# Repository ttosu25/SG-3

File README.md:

# Overview

Strain gauges produce very small differential voltage signals that encode information about mechanical strain. Precise and accurate measurement requires careful analogue signal conditioning before digitisation, followed by digital signal processing to extract the desired measurement. This project explores the design of a complete measurement device, from sensor excitation and analogue front-end conditioning through to digital acquisition, processing, and display output.

# System Block Diagram

# Key Design Features

## AC Current Excitation

Current-driven AC excitation: Current excitation improves the linearity between applied strain and differential bridge output. Using AC rather than DC excitation reduces measurement offset and drift, mitigates low frequency (1/f) noise, and suppresses parasitic thermoelectric effects.
  
## Bessel Filtering
The Bessel response was selected for its absence of overshoot and steeper amplitude roll-off compared with the Butterworth response. The filter also exhibits minimal passband variation and a simulated settling time of 7 ms, which is significantly shorter than the latency introduced by the sigma-delta ADC's digital filtering.

## Oversampled Sigma Delta ADC
Sigma-Delta converters contain integrated features such as digital filters that minimise the effect of extrinsic and intrinsic noise sources such as alias signal noise, 50/60hz power noise, RF noise pick up and clock jitter. The Oversampling nature of Sigma-Delta converts also distributes noise over a wider range of frequencies which reduces the effect of quantisation noise.

# Schematic

# PCB Layout and Tracing

# 3D model view

# Repository Structure

hardware/ — Contains the schematics, PCB layout files, Gerber files, MCU pin assignment, and hardware revisions.

tr/ — Contains technical research and supporting analysis, including datasheets, application notes, initial problem-space exploration, and SPICE simulations with FFT analysis.

docs/ — Contains the project specification, design documentation, and system diagrams.

firmware/ — Contains the programs running on the MCU for the embedded application.

Logbook entries not available.

# Status
Prototyping Stage, PCB fabricated.

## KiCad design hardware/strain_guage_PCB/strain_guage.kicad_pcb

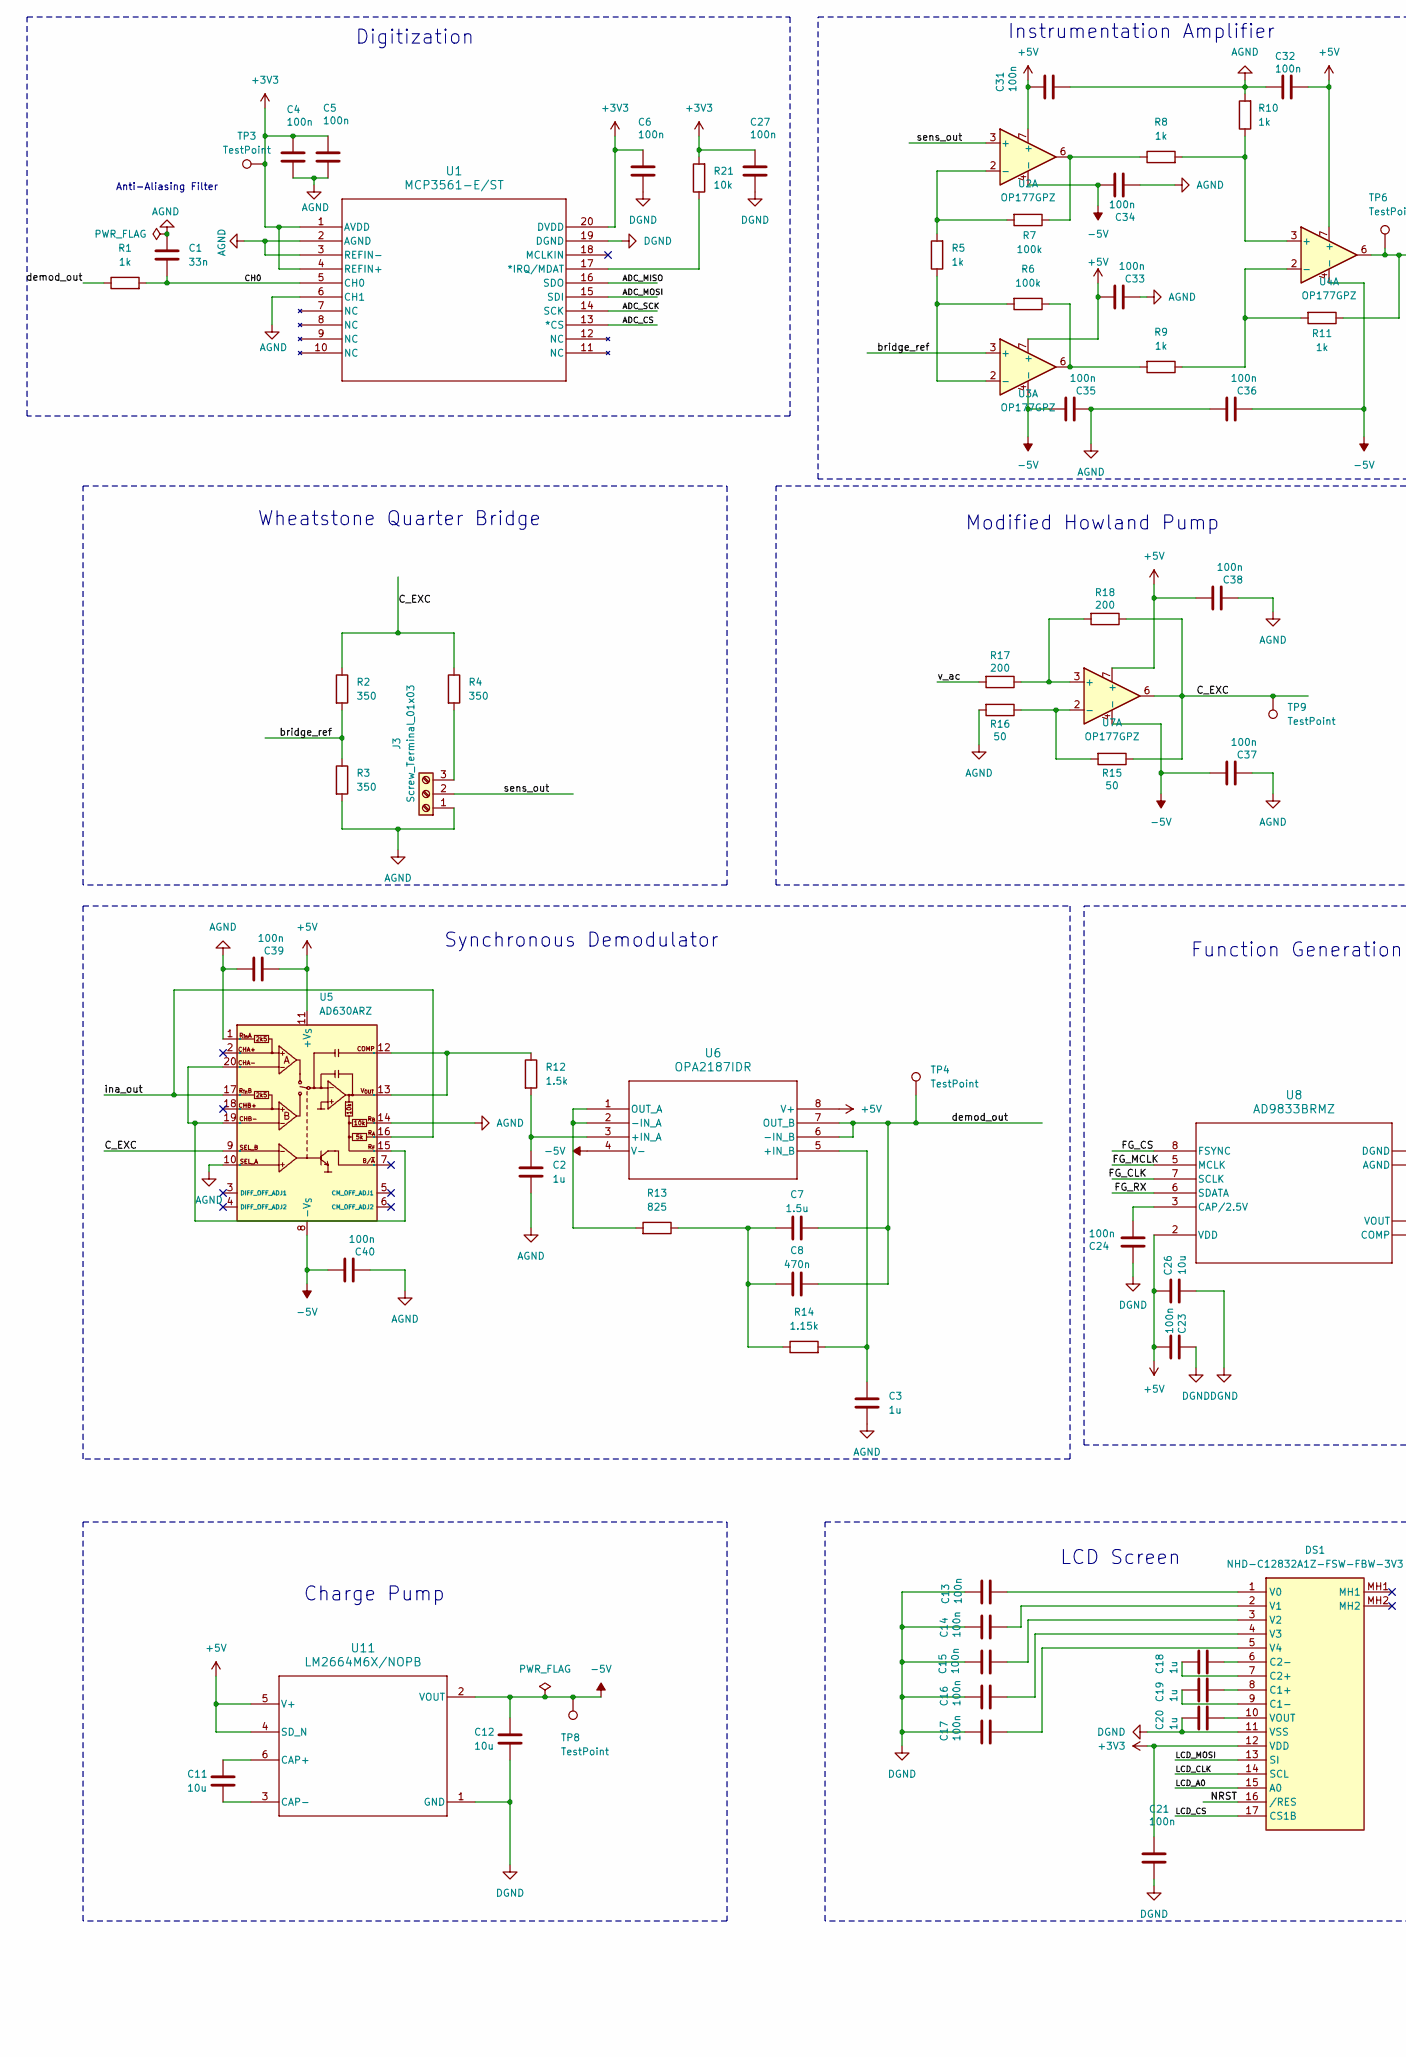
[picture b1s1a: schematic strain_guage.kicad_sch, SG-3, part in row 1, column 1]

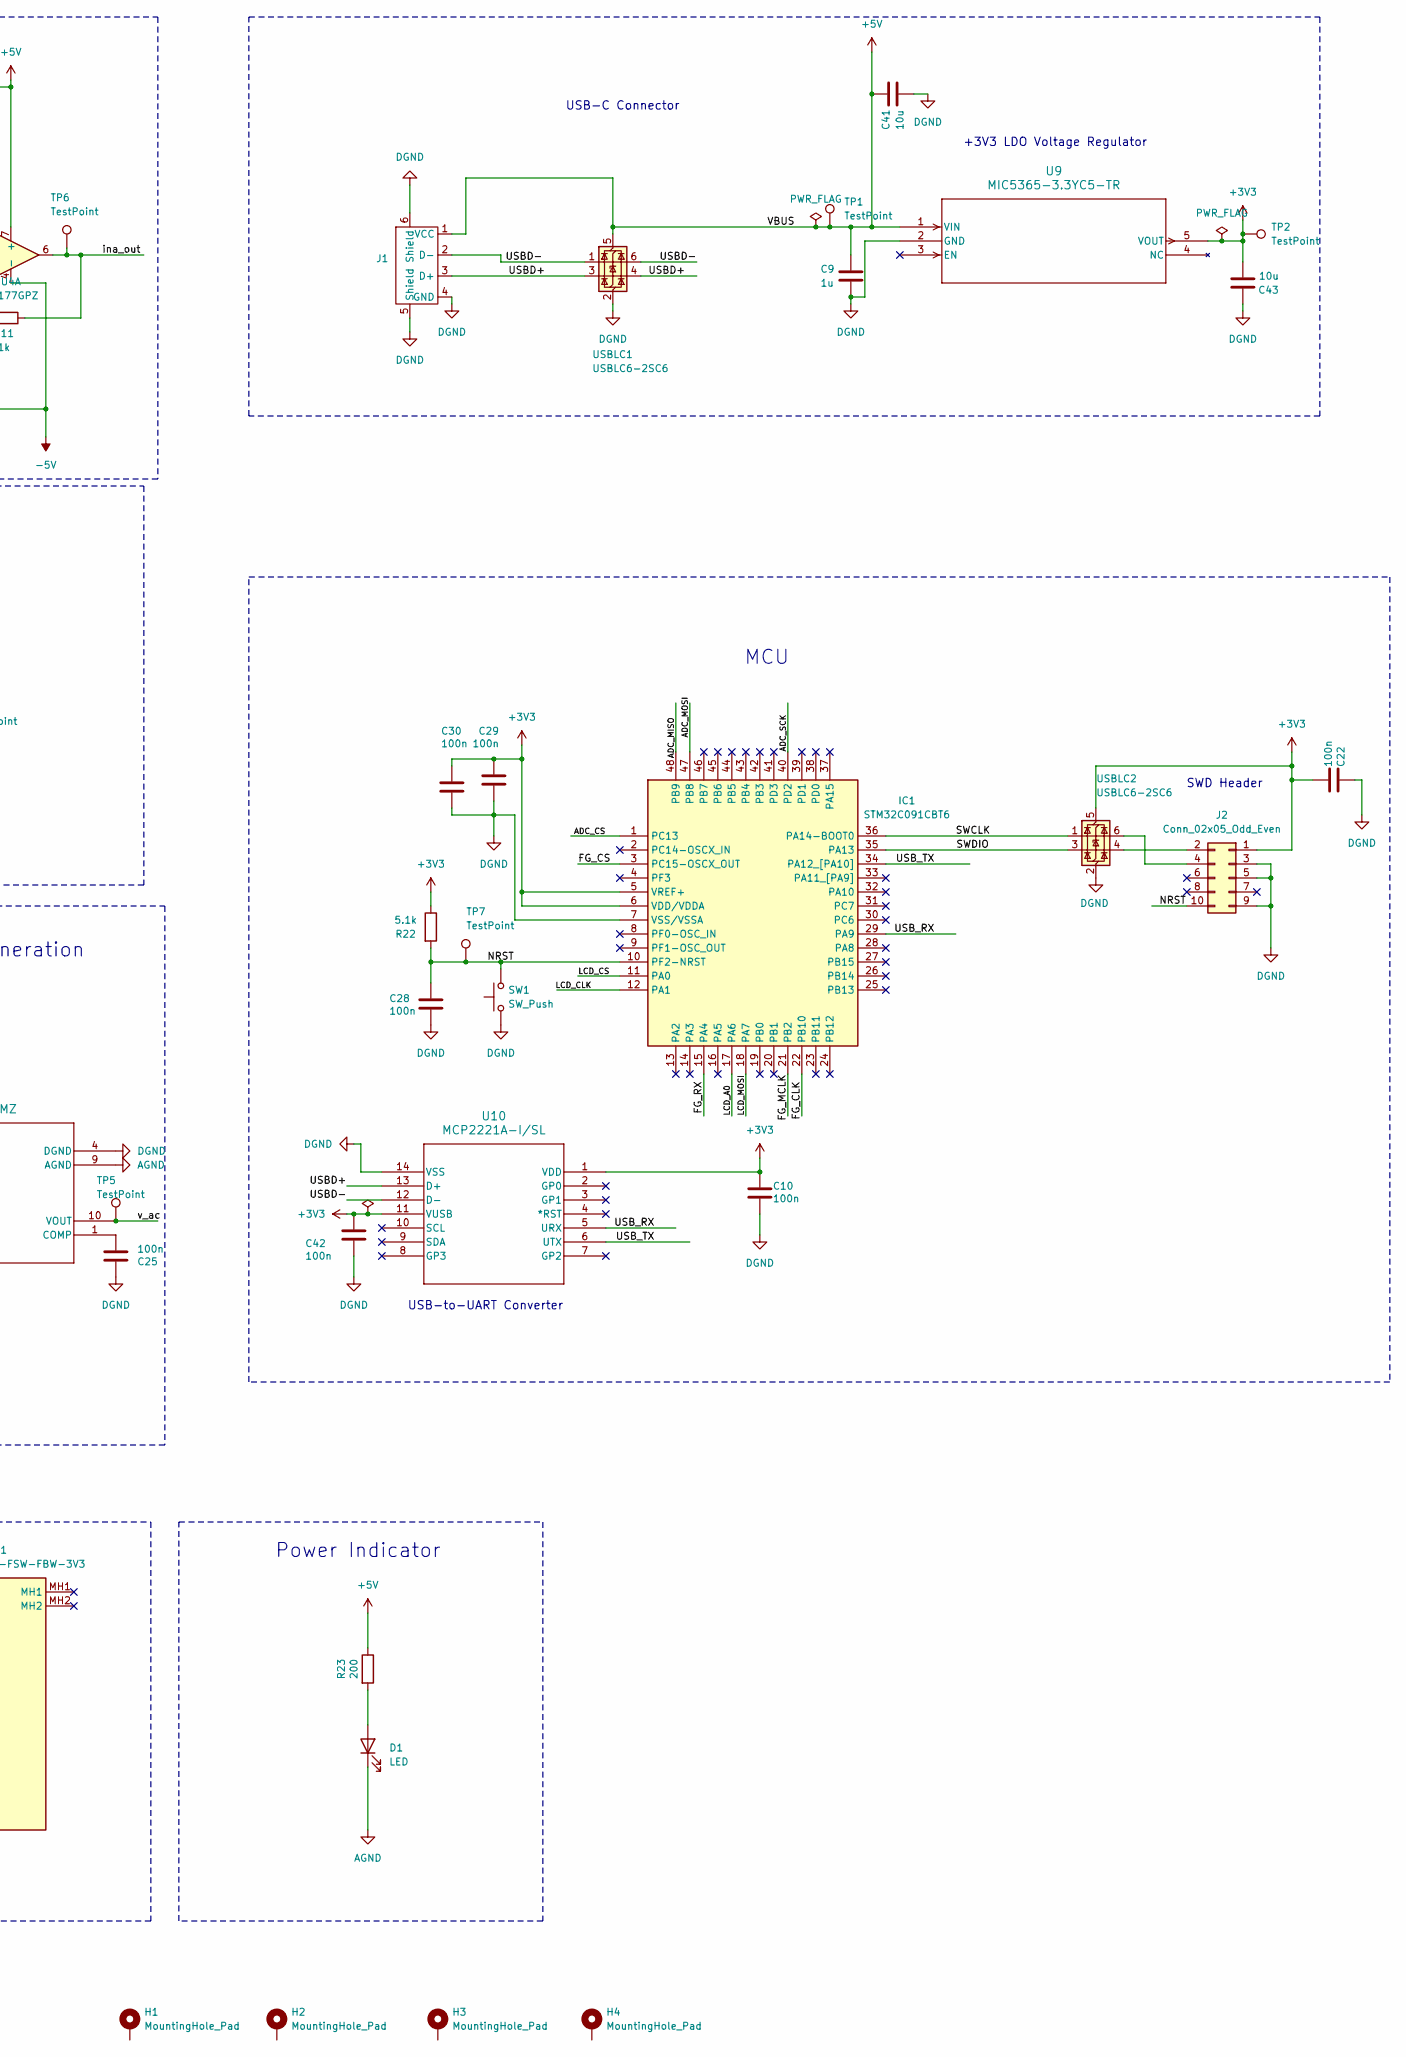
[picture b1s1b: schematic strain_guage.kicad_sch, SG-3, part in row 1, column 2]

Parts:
C1: 33n; C_0805_2012Metric_Pad1.18x1.45mm_HandSolder
C2, C3, C9, C18, C19, C20: 1u; C_0402_1005Metric
C4, C5, C6, C10, C13, C14, C15, C16, C17, C21, C22, C23, C24, C25, C27, C28, C29, C30, C31, C32, C33, C34, C35, C36, C37, C38, C39, C40, C42: 100n; C_0603_1608Metric_Pad1.08x0.95mm_HandSolder
C7: 1.5u; C_0805_2012Metric_Pad1.18x1.45mm_HandSolder
C8: 470n; C_1206_3216Metric_Pad1.33x1.80mm_HandSolder
C11, C12, C26, C41, C43: 10u; C_0402_1005Metric
D1: LED; LED_D5.0mm
DS1: NHD-C12832A1Z-FSW-FBW-3V3; NHDC12832A1ZFSWFBW3V3; Manufacturer_Part_Number NHD-C12832A1Z-FSW-FBW-3V3; Mouser Part Number 763-C12832A1ZFSWFBW3
H1, H2, H3, H4: MountingHole_Pad; MountingHole_3.2mm_M3_ISO7380_Pad
IC1: STM32C091CBT6; LQFP-48-1EP_7x7mm_P0.5mm_EP3.6x3.6mm; Manufacturer_Part_Number STM32C091CBT6
J1: USB-A-SMD_BX-TYPE-A-MWT4P
J2: Conn_02x05_Odd_Even; PinHeader_2x05_P1.27mm_Vertical_SMD
J3: Screw_Terminal_01x03; TerminalBlock_MaiXu_MX126-5.0-03P_1x03_P5.00mm
R1, R5, R8, R9, R10, R11: 1k; R_0603_1608Metric_Pad0.98x0.95mm_HandSolder
R2, R3, R4: 350; R_0603_1608Metric_Pad0.98x0.95mm_HandSolder
R6, R7: 100k; R_0805_2012Metric_Pad1.20x1.40mm_HandSolder
R12: 1.5k; R_1206_3216Metric
R13: 825; C_0402_1005Metric_Pad0.74x0.62mm_HandSolder
R14: 1.15k; C_0603_1608Metric_Pad1.08x0.95mm_HandSolder
R15, R16: 50; R_0603_1608Metric_Pad0.98x0.95mm_HandSolder
R17, R18, R23: 200; R_0402_1005Metric_Pad0.72x0.64mm_HandSolder
R21: 10k; R_0603_1608Metric_Pad0.98x0.95mm_HandSolder
R22: 5.1k; R_0402_1005Metric
SW1: SW_Push; SW_PUSH_6mm
TP1, TP2, TP3, TP4, TP5, TP6, TP7, TP8, TP9: TestPoint; TestPoint_Loop_D2.54mm_Drill1.5mm_Beaded
U1: MCP3561-E/ST; TSSOP20_ST_MCH
U2, U3, U4, U7: OP177GPZ; DIP794W56P254L959H533Q8N
U5: AD630ARZ; SOIC-20W_7.5x12.8mm_P1.27mm
U6: OPA2187IDR; D8_TEX
U8: AD9833BRMZ; RM_10_ADI
U9: MIC5365-3.3YC5-TR; SOT-353_SC-70-5_Handsoldering
U10: MCP2221A-I/SL; SOIC14_SL_MCH
U11: LM2664M6X/NOPB; DBV0006A_N
USBLC1, USBLC2: USBLC6-2SC6; SOT-23-6

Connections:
+3V3: C4.1, C5.1, C6.1, C10.1, C21.1, C22.2, C27.1, C29.1, C30.1, C42.1, C43.2, DS1.12 (VDD), IC1.5 (VREF+), IC1.6 (VDD/VDDA), J2.1 (VTREF), R21.2, R22.1, TP2.1, TP3.1, U1.1 (AVDD), U1.4 (REFIN+), U1.20 (DVDD), U9.5 (VOUT), U10.1 (VDD), U10.11 (VUSB), USBLC2.5 (VBUS)
+5V: C9.1, C23.2, C26.1, C31.1, C32.1, C33.1, C38.1, C39.2, C41.1, J1.1 (VCC), R23.1, TP1.1, U2.7 (+), U3.7 (+), U4.7 (+), U5.11 (+V_{S}), U6.8 (V+), U7.7 (+), U8.2 (VDD), U9.1 (VIN), U11.4 (SD_N), U11.5 (V+), USBLC1.5 (VBUS)
-5V: C12.1, C34.1, C35.1, C36.2, C37.1, C40.1, TP8.1, U2.4 (-), U3.4 (-), U4.4 (-), U5.8 (-V_{S}), U6.4 (V-), U7.4 (-), U11.2 (VOUT)
/ADC_CS: IC1.1 (PC13), U1.13 (*CS)
/ADC_MISO: IC1.48 (PB9), U1.16 (SDO)
/ADC_MOSI: IC1.47 (PB8), U1.15 (SDI)
/ADC_SCK: IC1.40 (PD2), U1.14 (SCK)
/CH0: C1.2, R1.2, U1.5 (CH0)
/C_EXC: R2.1, R4.1, R15.1, R18.1, TP9.1, U5.9 (SEL_B), U7.6
/FG_CLK: IC1.22 (PB10), U8.7 (SCLK)
/FG_CS: IC1.3 (PC15-OSCX_OUT), U8.8 (FSYNC)
/FG_MCLK: IC1.21 (PB2), U8.5 (MCLK)
/FG_RX: IC1.15 (PA4), U8.6 (SDATA)
/LCD_A0: DS1.15 (A0), IC1.17 (PA6)
/LCD_CLK: DS1.14 (SCL), IC1.12 (PA1)
/LCD_CS: DS1.17 (CS1B), IC1.11 (PA0)
/LCD_MOSI: DS1.13 (SI), IC1.18 (PA7)
/NRST: C28.1, DS1.16 (/RES), IC1.10 (PF2-NRST), J2.10 (NRST), R22.2, SW1.2, TP7.1
/SWCLK: IC1.36 (PA14-BOOT0), USBLC2.1 (I/O1)
/SWDIO: IC1.35 (PA13), USBLC2.3 (I/O2)
/USBD+: J1.3 (D+), U10.13 (D+), USBLC1.3 (I/O2), USBLC1.4 (I/O2)
/USBD-: J1.2 (D-), U10.12 (D-), USBLC1.1 (I/O1), USBLC1.6 (I/O1)
/USB_RX: IC1.29 (PA9), U10.5 (URX)
/USB_TX: IC1.34 (PA12_[PA10]), U10.6 (UTX)
/bridge_ref: R2.2, R3.1, U3.3 (+)
/demod_out: C7.2, C8.2, R1.1, TP4.1, U6.6 (-IN_B), U6.7 (OUT_B)
/ina_out: R11.1, TP6.1, U4.6, U5.16 (R_{A}), U5.17 (R_{in}B)
/sens_out: J3.2, U2.3 (+)
/v_ac: R17.2, TP5.1, U8.10 (VOUT)
AGND: C1.1, C2.2, C3.2, C4.2, C5.2, C31.2, C32.2, C33.2, C34.2, C35.2, C36.1, C37.2, C38.2, C39.1, C40.2, D1.1 (K), J3.1, R3.2, R10.2, R16.2, U1.2 (AGND), U1.3 (REFIN-), U1.6 (CH1), U5.1 (R_{in}A), U5.10 (SEL_A), U5.14 (R_{B}), U8.9 (AGND)
DGND: C6.2, C9.2, C10.2, C12.2, C13.1, C14.1, C15.1, C16.1, C17.1, C20.1, C21.2, C22.1, C23.1, C24.1, C25.1, C26.2, C27.2, C28.2, C29.2, C30.2, C41.2, C42.2, C43.1, DS1.11 (VSS), IC1.7 (VSS/VSSA), J1.4 (GND), J1.5 (Shield), J1.6 (Shield), J2.3 (GND), J2.5 (GND), J2.9 (GND), SW1.1, U1.19 (DGND), U8.4 (DGND), U9.2 (GND), U10.14 (VSS), U11.1 (GND), USBLC1.2 (GND), USBLC2.2 (GND)
unnamed: C7.1, C8.1, R13.1, R14.1
unnamed: D1.2 (A), R23.2
unnamed: C19.2, DS1.8 (C1+)
unnamed: C19.1, DS1.9 (C1-)
unnamed: C18.1, DS1.7 (C2+)
unnamed: C18.2, DS1.6 (C2-)
unnamed: C13.2, DS1.1 (V0)
unnamed: C14.2, DS1.2 (V1)
unnamed: C15.2, DS1.3 (V2)
unnamed: C16.2, DS1.4 (V3)
unnamed: C17.2, DS1.5 (V4)
unnamed: C20.2, DS1.10 (VOUT)
unnamed: J2.4 (SWCLK), USBLC2.6 (I/O1)
unnamed: J2.2 (SWDIO), USBLC2.4 (I/O2)
unnamed: J3.3, R4.2
unnamed: R5.1, R6.2, U3.2 (-)
unnamed: R5.2, R7.2, U2.2 (-)
unnamed: R6.1, R9.2, U3.6
unnamed: R7.1, R8.1, U2.6
unnamed: R8.2, R10.1, U4.3 (+)
unnamed: R9.1, R11.2, U4.2 (-)
unnamed: R15.2, R16.1, U7.2 (-)
unnamed: R17.1, R18.2, U7.3 (+)
unnamed: R21.1, U1.17 (*IRQ/MDAT)
unnamed: U5.15 (R_{F}), U5.19 (CHB-), U5.20 (CHA-)
unnamed: R12.1, U5.12 (COMP), U5.13 (V_{OUT})
unnamed: C2.1, R12.2, U6.3 (+IN_A)
unnamed: C3.1, R14.2, U6.5 (+IN_B)
unnamed: R13.2, U6.1 (OUT_A), U6.2 (-IN_A)
unnamed: C24.2, U8.3 (CAP/2.5V)
unnamed: C25.2, U8.1 (COMP)
unnamed: C11.1, U11.6 (CAP+)
unnamed: C11.2, U11.3 (CAP-)

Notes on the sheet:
Wheatstone Quarter Bridge
Modified Howland Pump
USB-to-UART Converter
Anti-Aliasing Filter
MCU
+3V3 LDO Voltage Regulator
Function Generation
SWD Header
Digitization
Instrumentation Amplifier
Power Indicator
Charge Pump
USB-C Connector
LCD Screen
Synchronous Demodulator

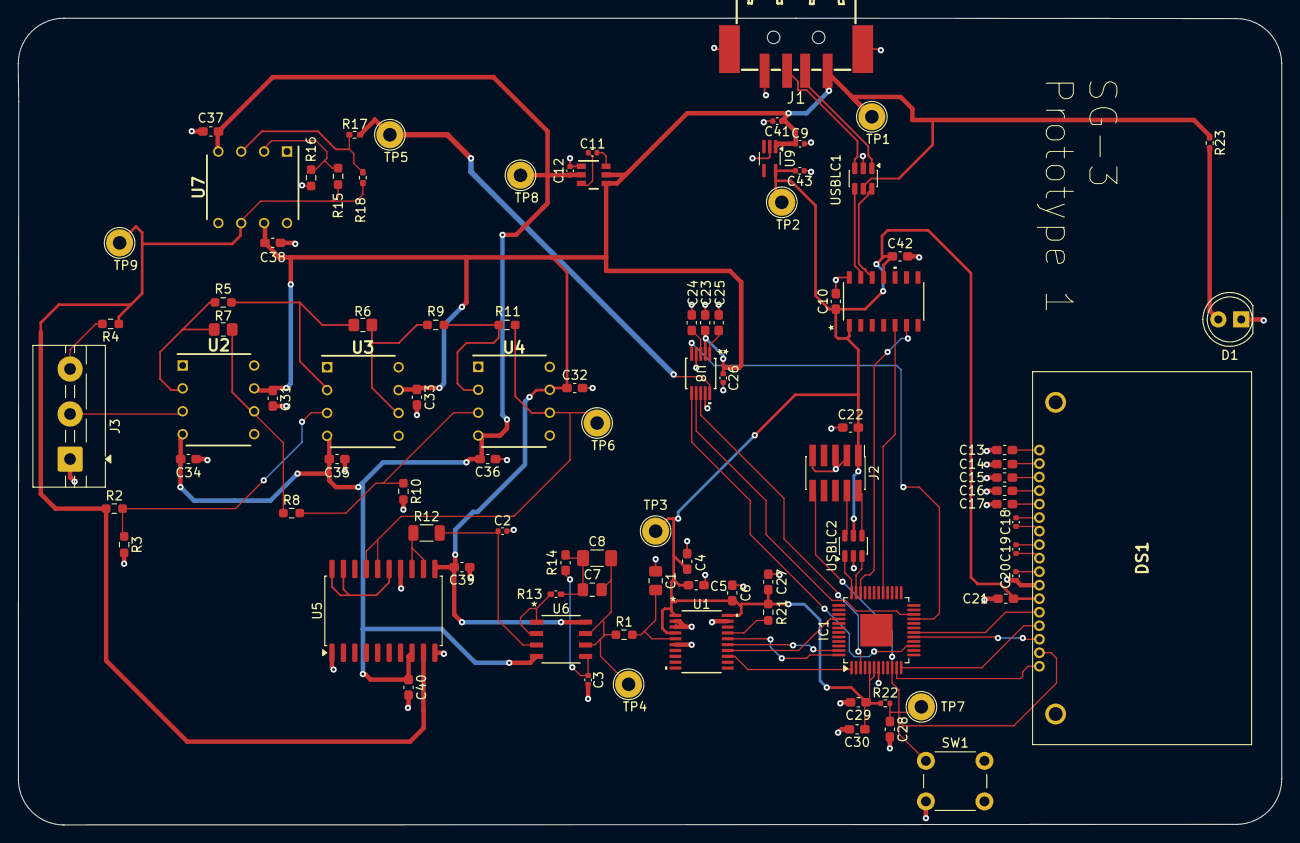
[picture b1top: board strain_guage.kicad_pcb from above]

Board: 4 copper layers, 140.3 x 89.5 mm, 93 parts (0 on the bottom side), 64 nets.

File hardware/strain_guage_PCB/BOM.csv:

Reference,Qty,Value,DNP,Exclude from BOM,Exclude from Board,Footprint,Distributor Link,DistributorLink,Height,Manufacturer,Manufacturer_Name,Manufacturer_Part_Number,Mouser Part Number,Mouser Price/Stock,Price,Description
C1,1,33n,,,,Capacitor_SMD:C_0805_2012Metric_Pad1.18x1.45mm_HandSolder,,https://uk.farnell.com/kemet/c0805c333f3gactu/cap-0-033uf-25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,,YAGEO KEMET,,,,, Â£2.95,"Multilayer Ceramic Capacitor,"
"C2,C3,C9,C18,C19,C20",6,1u,,,,Capacitor_SMD:C_0402_1005Metric,,https://www.digikey.co.uk/en/products/detail/tdk/C1005X6S1C1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,,TDK,,,,,Â£0.08,Ceramic Capacitor
"C4,C5,C6,C10,C13,C14,C15,C16,C17,C21,C22,C23,C24,C25,C27,C28,C29,C30,C31,C32,C33,C34,C35,C36,C37,C38,C39,C40,C42",29,100n,,,,Capacitor_SMD:C_0603_1608Metric_Pad1.08x0.95mm_HandSolder,,,,YAGEO KEMET,,,,,,Multilayer ceramic capacitor
C7,1,1.5u,,,,Capacitor_SMD:C_0805_2012Metric_Pad1.18x1.45mm_HandSolder,,https://www.digikey.co.uk/en/products/detail/tdk/C2012X7R1H1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,,TDK,,,,,$0.63,Multilayer Ceramic Capacitor
C8,1,470n,,,,Capacitor_SMD:C_1206_3216Metric_Pad1.33x1.80mm_HandSolder,,https://www.digikey.co.uk/en/products/detail/kemet/C1206C474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,,KEMET,,,,,$0.56,Multilayer Ceramic Capacitor
"C11,C12,C26,C41,C43",5,10u,,,,Capacitor_SMD:C_0402_1005Metric,,https://www.digikey.co.uk/en/products/detail/murata-electron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,,  Murata Electronics,,,,,$0.1,Ceramic Capacitor
D1,1,LED,,,,LED_THT:LED_D5.0mm,,https://www.digikey.co.uk/en/products/detail/w-rth-elektroni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,,Würth Elektronik,,,,,$0.25,Light emitting diode
DS1,1,NHD-C12832A1Z-FSW-FBW-3V3,,,,NHDC12832A1ZFSWFBW3V3,https://www.digikey.co.uk/en/products/detail/newhaven-displa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,,4.3,,Newhaven Display,NHD-C12832A1Z-FSW-FBW-3V3,763-C12832A1ZFSWFBW3,https://www.mouser.co.uk/ProductDetail/Newhaven-Display/NHD-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,$10.95,LCD Graphic Display Modules & Accessories FSTN (+) 41.4 x 24.3 x 4.0
"H1,H2,H3,H4",4,MountingHole_Pad,,Excluded from BOM,,MountingHole:MountingHole_3.2mm_M3_ISO7380_Pad,,,,,,,,,,Mounting Hole with connection
IC1,1,STM32C091CBT6,,,,Package_QFP:LQFP-48-1EP_7x7mm_P0.5mm_EP3.6x3.6mm,,https://www.digikey.co.uk/en/products/detail/stmicroelectron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,1.6,,STMicroelectronics,STM32C091CBT6,,,$2.21,"Mainstream Arm Cortex-M0+ MCU with 128 Kbytes of Flash memory, 36 Kbytes RAM, 48 MHz CPU, 4x USART, timers, ADC, comm. I/F, 2-3.6V"
J1,1,USB_C_Receptacle_USB2.0_16P,,,,USBC:UJ20CHGMSMT4BP16TR,,https://www.mouser.co.uk/en/ProductDetail/Same-Sky/UJ20-C-H-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,,Same Sky,,,,,£0.35,USB Connectors USB Type C Recept RA Mid-Mnt SMT
J2,1,Conn_02x05_Odd_Even,,,,Connector_PinHeader_1.27mm:PinHeader_2x05_P1.27mm_Vertical_SMD,,https://www.digikey.co.uk/en/products/detail/samtec-inc/FTSH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,,Samtec Inc,,,,,$1.37,"Generic connector, double row, 02x05, odd/even pin numbering scheme (row 1 odd numbers, row 2 even numbers), script generated (kicad-library-utils/schlib/autogen/connector/)"
J3,1,Screw_Terminal_01x03,,,,TerminalBlock_MaiXu_MX126-5.0-03P_1x03_P5.00mm,,,,,,,,,,"Generic screw terminal, single row, 01x03, script generated (kicad-library-utils/schlib/autogen/connector/)"
"R1,R5,R8,R9,R10,R11",6,1k,,,,Resistor_SMD:R_0603_1608Metric_Pad0.98x0.95mm_HandSolder,,https://uk.farnell.com/multicomp-pro/mcwf06r1001btl/res-1k-0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,,MULTICOMP PRO,,,,,,Resistor
"R2,R3,R4",3,350,,,,Resistor_SMD:R_0603_1608Metric_Pad0.98x0.95mm_HandSolder,,https://uk.farnell.com/vpg-foil-resistors/y4021350r000d9r/re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,,VPG FOIL RESISTORS,,,,,Â£11.304,Resistor
"R6,R7",2,100k,,,,Resistor_SMD:R_0805_2012Metric_Pad1.20x1.40mm_HandSolder,,https://uk.farnell.com/koa/rs73f2attd1003b/res-100k-0-1-0-25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,,KOA,,,,,Â£0.312,Resistor
R12,1,1.5k,,,,Resistor_SMD:R_1206_3216Metric,,https://uk.farnell.com/vishay/ptn1206y1501bst1/res-1k5-0-1-0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,,VISHAY,,,,,Â£1.680,Resistor
R13,1,825,,,,Capacitor_SMD:C_0402_1005Metric_Pad0.74x0.62mm_HandSolder,,https://www.mouser.co.uk/en/ProductDetail/Vishay/TNPW0402825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,,VISHAY,,,,,Â£0.196,Thin Fil Resistor
R14,1,1.15k,,,,Capacitor_SMD:C_0603_1608Metric_Pad1.08x0.95mm_HandSolder,,https://www.mouser.co.uk/en/ProductDetail/YAGEO/RT0603BRC071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,,YAGEO,,,,,Â£0.225,Thin Film Resistor
"R15,R16",2,50,,,,Resistor_SMD:R_0603_1608Metric_Pad0.98x0.95mm_HandSolder,,https://www.digikey.co.uk/en/products/detail/vishay-dale/CRC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,,VISHAY DALE,,,,,$0.10,Resistor
"R17,R18,R23",3,200,,,,Resistor_SMD:R_0402_1005Metric_Pad0.72x0.64mm_HandSolder,,https://www.digikey.co.uk/en/products/detail/panasonic-indus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,,PANASONIC INDUSTRY,,,,,$0.10,Resistor
R22,1,5.1k,,,,Resistor_SMD:R_0201_0603Metric,,https://uk.farnell.com/multicomp-pro/mcre000157/res-5k1-1-0-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,,MULTICOMP PRO,,,,,,Resistor
R21,1,10k,,,,Resistor_SMD:R_0603_1608Metric_Pad0.98x0.95mm_HandSolder,,https://uk.farnell.com/vishay/crcw060310k0fkea/res-10k-1-0-1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,,VISHAY,,,,,Â£0.13,Resistor
SW1,1,SW_Push,,,,Button_Switch_THT:SW_PUSH_6mm,,https://uk.farnell.com/multicomp-pro/mcdts6-5n/tactile-switc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,,MULTICOMP PRO,,,,,Â£0.18,"Push button switch, generic, two pins"
"TP1,TP2,TP3,TP4,TP5,TP6,TP7,TP8,TP9",9,TestPoint,,,,TestPoint:TestPoint_Loop_D2.54mm_Drill1.5mm_Beaded,,,,,,,,,,test point
U1,1,MCP3561-E/ST,,,,TSSOP20_ST_MCH,,https://uk.farnell.com/microchip/mcp3561rt-e-nc/adc-24bit-15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,,,,,,,Â£2.30,"2-channel, 24-bit, Delta-Sigma Analog-to-Digital Converters (ADCs) with programmable data rate of up to 153.6 ksps"
"U2,U3,U4,U7",4,OP177GPZ,,,,Package_SO:SOIC-8_5.3x5.3mm_P1.27mm,,https://uk.farnell.com/analog-devices/op177gpz/opamp-dip-8-6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,,ADI,,,,,Â£4.512,"low noise, bipolar input operational amplifier"
U5,1,AD630ARZ,,,,Package_SO:SOIC-20W_7.5x12.8mm_P1.27mm,,,,,,,,,,"High precision Balanced Modulator/Demodulator, 2 MHz, SOIC-20W"
U6,1,OPA2187IDR,,,,D8_TEX,,,,,,,,,,
U8,1,AD9833BRMZ,,,,RM_10_ADI,,,,,,,,,,
U9,1,MIC5365-3.3YC5-TR,,,,Package_TO_SOT_SMD:TSOT-23-5,,https://www.digikey.co.uk/en/products/detail/microchip-techn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,,,,,,,Â£$0.12,Linear Voltage Regulator IC Positive Fixed 1 Output 150mA SC-70-5
U10,1,MCP2221A-I/SL,,,,SOIC14_SL_MCH,,,,,,,,,,
U11,1,LM2664M6X/NOPB,,,,DBV0006A_N,,,,,,,,,,
"USBLC1,USBLC2",2,USBLC6-2SC6,,,,Package_TO_SOT_SMD:SOT-23-6,,https://www.digikey.co.uk/en/products/detail/stmicroelectron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,,,,,,,Â£0.43,"Very low capacitance ESD protection diode, 2 data-line, SOT-23-6"

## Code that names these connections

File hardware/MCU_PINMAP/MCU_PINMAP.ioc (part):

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Mcu.Name=STM32C091CBTx
Mcu.Package=LQFP48
Mcu.UserName=STM32C091CBTx
PA0.Signal=GPIO_Output
PA1.Signal=SPI1_SCK
PA10.Signal=USART1_RX
PA13.Mode=Serial_Wire
PA13.Signal=DEBUG_SWDIO
PA14-BOOT0.Mode=Serial_Wire
PA14-BOOT0.Signal=DEBUG_SWCLK
PA3.Signal=GPIO_Output
PA4.Signal=SPI2_MOSI
PA5.Signal=GPIO_Output
PA6.Signal=SPI1_MISO
PA7.Signal=SPI1_MOSI
PA9.Signal=USART1_TX
PB10.Signal=SPI2_SCK
PB2.Mode=Clock-out2
PB2.Signal=RCC_MCO_2
PB8.Signal=USART3_TX
PB9.Signal=USART3_RX
PC13.Signal=GPIO_Output
PC15-OSCX_OUT(PC15).Signal=GPIO_Output
PD2.Signal=USART3_CK
RCC.HSE_VALUE=8000000
RCC.SYSCLKFreq_VALUE=12000000
board=custom
